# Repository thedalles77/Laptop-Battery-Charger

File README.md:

# Laptop-Battery-Charger
This repository has all the files that I used to repurpose a Dell D630 laptop into a portable Raspberry Pi. 

The Instructable "Battery Powered Raspberry Pi in Repurposed Laptop" is at this url:

https://www.instructables.com/Battery-Powered-Raspberry-Pi-in-Repurposed-Laptop/

The Video "Portable Raspberry Pi Laptop with a Custom Battery Charger" is at this url:

https://vimeo.com/504006511

The Max1873 based battery charge controller board shown below is detailed as a 
Hackster.IO project at this url:

https://www.hackster.io/frank-adams/laptop-battery-charge-controller-e9c3dc

The MP26123 based battery charge controller board shown below is detailed as a 
Hackaday.IO project at this url:

https://hackaday.io/project/177700/details/

A battery fuel gauge using Cairo can be found at this location: 
https://github.com/thedalles77/Raspberry-Pi-easy-drawing

The folders at this repo are organized as follows:

  AT Tiny Supervisor folder contains the AT Tiny 85 code to supervise the charging of a 3 series or 4 series wired battery pack.
  
  Eagle_Board_Files folder contains two folders: One for the Max1873 board and one for the MP26123_4 board. They contain the Eagle layout and schematic, parts list, and test procedure.
  
  Dell_D630_Portable_Pi_KVM folder contains the keyboard matrix and Teensy 3.2 Arduino code for controlling the keyboard, touchpad, and video converter card.
  
  My_Ugly_C_Code folder contains the Pi C code that reads the battery status registers over the SMBus.
  
  USB_SMBUS_CP2112 folder contains the Eagle board files to build a USB to SM Bus bridge for reading the battery status registers. See https://github.com/thedalles77/cp2112_demo for the code to display the battery status registers.
  
  Load_Switch_NCP_45760 folder contains the Eagle board files to build a load switch using the On Semiconductor NCP45760 chip.

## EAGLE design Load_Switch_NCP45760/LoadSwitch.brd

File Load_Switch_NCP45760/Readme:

I had problems getting this NCP45760IMN24RTWG load switch to work but I'll provide the information in case someone else has better luck. 
Let me know if you find a way to make it work.
The Eagle board and schematic files are provided along with pictures.
The 3.3 volt regulator can be an AP7381-33V-A through hole or the AP7381-33Y-13 SMD. The caps are 0805 case size and the resistors are 0603 size.
The loads on the switch were two LM2596 buck regulators that provided 10 volts to the video card and 5 volts to the Pi. 
Each buck regulator had a 100uf cap on its input and a 220uf cap on its output with more caps on the Pi and video card.
The input voltage was 19 Volts DC from a wall supply.
I started with the overcurrent resistor R2 set at 10K and the slew rate capacitor C4 set to 0.01uf but this caused the current protection circuit to trip when first enabled.
Changing the R2 resistor to a short did not change anything but changing the C4 slew rate cap to 1uf allowed the switch to work without tripping the protection circuit.
It ran for 30 minutes and the temperature on the chip and input/output traces stabilized at 52 deg C.
Unfortuantely the load switch would not turn off so I apparently ruined the chip by setting the slew rate to a very slow value.
Even changing the slew rate cap to 0.1uf will still exceed the Energy rating based on the formulas in the data sheet.
This leads me to believe that this chip is not usable for my configuration but it may work fine at lower voltages and/or lower currents.

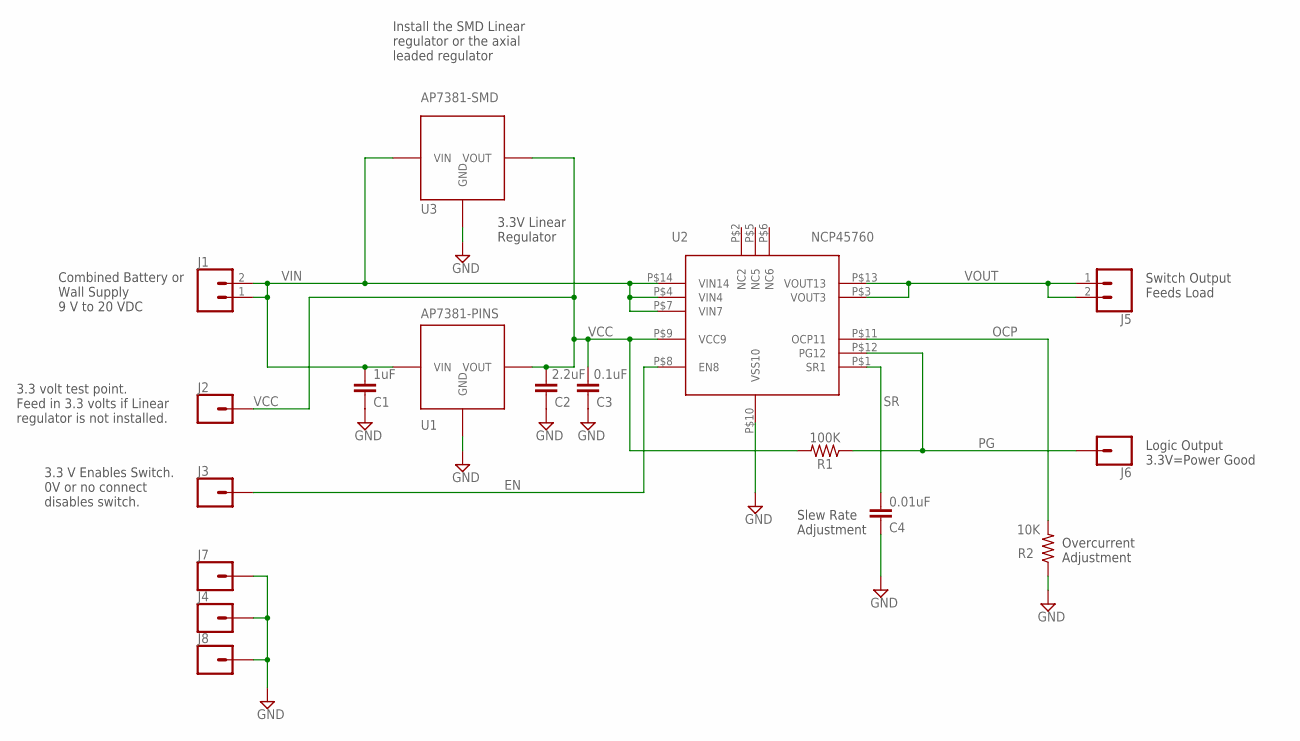
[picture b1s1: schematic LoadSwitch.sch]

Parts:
C1: 1uF; 0805_CAP
C2: 2.2uF; 0805_CAP
C3: 0.1uF; 0805_CAP
C4: 0.01uF; 0805_CAP
J1, J5: CONN_02; 1X02
J2, J3, J4, J6, J7, J8: CONN_01; 1X01
R1: 100K; 0603_RESISTOR
R2: 10K; 0603_RESISTOR
U1: AP7381-PINS; AP7381_PINS
U2: NCP45760
U3: AP7381-SMD; AP7381

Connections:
EN: J3.1, U2.P$8 (EN8)
GND: C1.2, C2.2, C3.2, C4.2, J4.1, J7.1, J8.1, R2.1, U1.P$2 (GND), U2.P$10 (VSS10), U3.P$3 (GND), U3.P$4 (GND)
OCP: R2.2, U2.P$11 (OCP11)
PG: J6.1, R1.1, U2.P$12 (PG12)
SR: C4.1, U2.P$1 (SR1)
VCC: C2.1, C3.1, J2.1, R1.2, U1.P$1 (VOUT), U2.P$9 (VCC9), U3.P$1 (VOUT)
VIN: C1.1, J1.1, J1.2, U1.P$3 (VIN), U2.P$4 (VIN4), U2.P$7 (VIN7), U2.P$14 (VIN14), U3.P$2 (VIN)
VOUT: J5.1, J5.2, U2.P$3 (VOUT3), U2.P$13 (VOUT13)

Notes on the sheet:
3.3V Linear Regulator
Combined Battery or Wall Supply 9 V to 20 VDC
3.3 volt test point. Feed in 3.3 volts if Linear regulator is not installed.
3.3 V Enables Switch. 0V or no connect disables switch.
Slew Rate Adjustment
Overcurrent Adjustment
Switch Output Feeds Load
Logic Output 3.3V=Power Good
Install the SMD Linear regulator or the axial leaded regulator

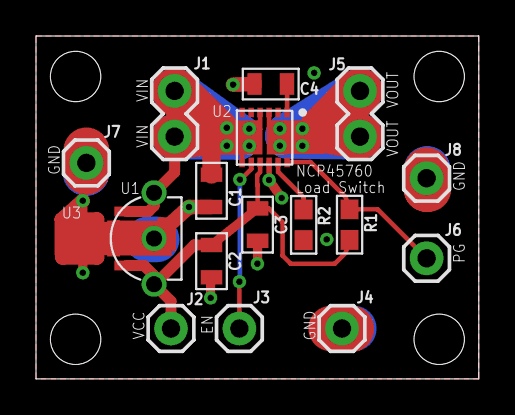
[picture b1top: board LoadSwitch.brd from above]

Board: 2 copper layers, 24.6 x 19.1 mm, 18 parts (1 on the bottom side), 8 nets.

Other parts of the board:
U$1: OSHW_5MM

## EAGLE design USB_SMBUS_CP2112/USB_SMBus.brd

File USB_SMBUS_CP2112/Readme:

See Step 15 of my Instructable for more information regarding the CP2112:
https://www.instructables.com/Battery-Powered-Raspberry-Pi-in-Repurposed-Laptop/
See the forked version of Nick Dademo's repo for the modified code:
https://github.com/thedalles77/cp2112_demo

The Eagle brd file includes the recommended footprint for the slotted holes on the USB connector.
To fabricate this board at OSH Park, upload the zip file which has been run thru a CAM processor to create the proper slotted holes.

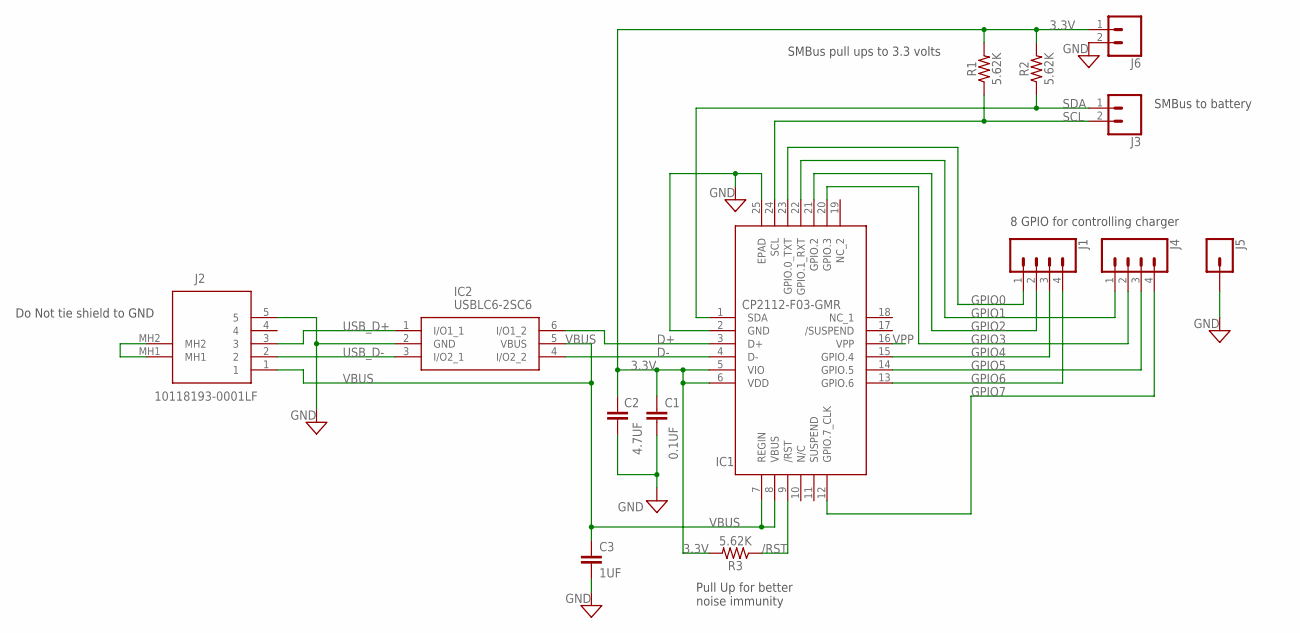
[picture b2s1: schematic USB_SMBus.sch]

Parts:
C1: 0.1UF; 0805_CAP
C2: 4.7UF; 0805_CAP
C3: 1UF; 0805_CAP
IC1: CP2112-F03-GMR; QFN50P400X400X80-25N
IC2: USBLC6-2SC6; SOT95P280X145-6N
J1, J4: CONN_04; 1X04
J2: 10118193-0001LF; 101181930001LF
J3, J6: CONN_02; 1X02
J5: CONN_01; 1X01
R1, R2, R3: 5.62K; 0603_RESISTOR

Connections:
3.3V: C1.1, C2.1, IC1.5 (VIO), IC1.6 (VDD), J6.1, R1.2, R2.2, R3.2
/RST: IC1.9 (/RST), R3.1
D+: IC1.3 (D+), IC2.6 (I/O1_2)
D-: IC1.4 (D-), IC2.4 (I/O2_2)
GND: C1.2, C2.2, C3.2, IC1.2 (GND), IC1.25 (EPAD), IC2.2 (GND), J2.5, J5.1, J6.2
GPIO0: IC1.23 (GPIO.0_TXT), J1.1
GPIO1: IC1.22 (GPIO.1_RXT), J4.1
GPIO2: IC1.21 (GPIO.2), J1.2
GPIO3: IC1.20 (GPIO.3), J4.2
GPIO4: IC1.15 (GPIO.4), J1.3
GPIO5: IC1.14 (GPIO.5), J4.3
GPIO6: IC1.13 (GPIO.6), J1.4
GPIO7: IC1.12 (GPIO.7_CLK), J4.4
unnamed: J2.MH1, J2.MH2
SCL: IC1.24 (SCL), J3.2, R1.1
SDA: IC1.1 (SDA), J3.1, R2.1
USB_D+: IC2.1 (I/O1_1), J2.3
USB_D-: IC2.3 (I/O2_1), J2.2
VBUS: C3.1, IC1.7 (REGIN), IC1.8 (VBUS), IC2.5 (VBUS), J2.1
VPP: IC1.16 (VPP)

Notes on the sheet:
Pull Up for better noise immunity
Do Not tie shield to GND
SMBus to battery
8 GPIO for controlling charger
SMBus pull ups to 3.3 volts

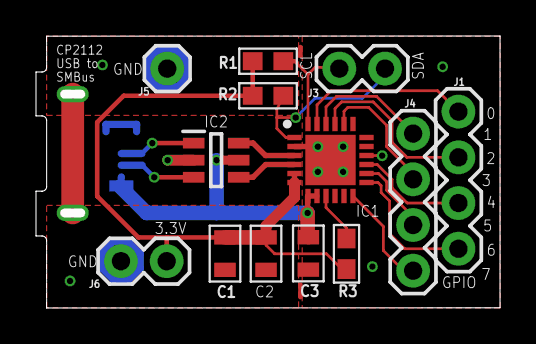
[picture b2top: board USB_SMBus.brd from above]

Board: 2 copper layers, 25.3 x 14.6 mm, 14 parts (1 on the bottom side), 19 nets.

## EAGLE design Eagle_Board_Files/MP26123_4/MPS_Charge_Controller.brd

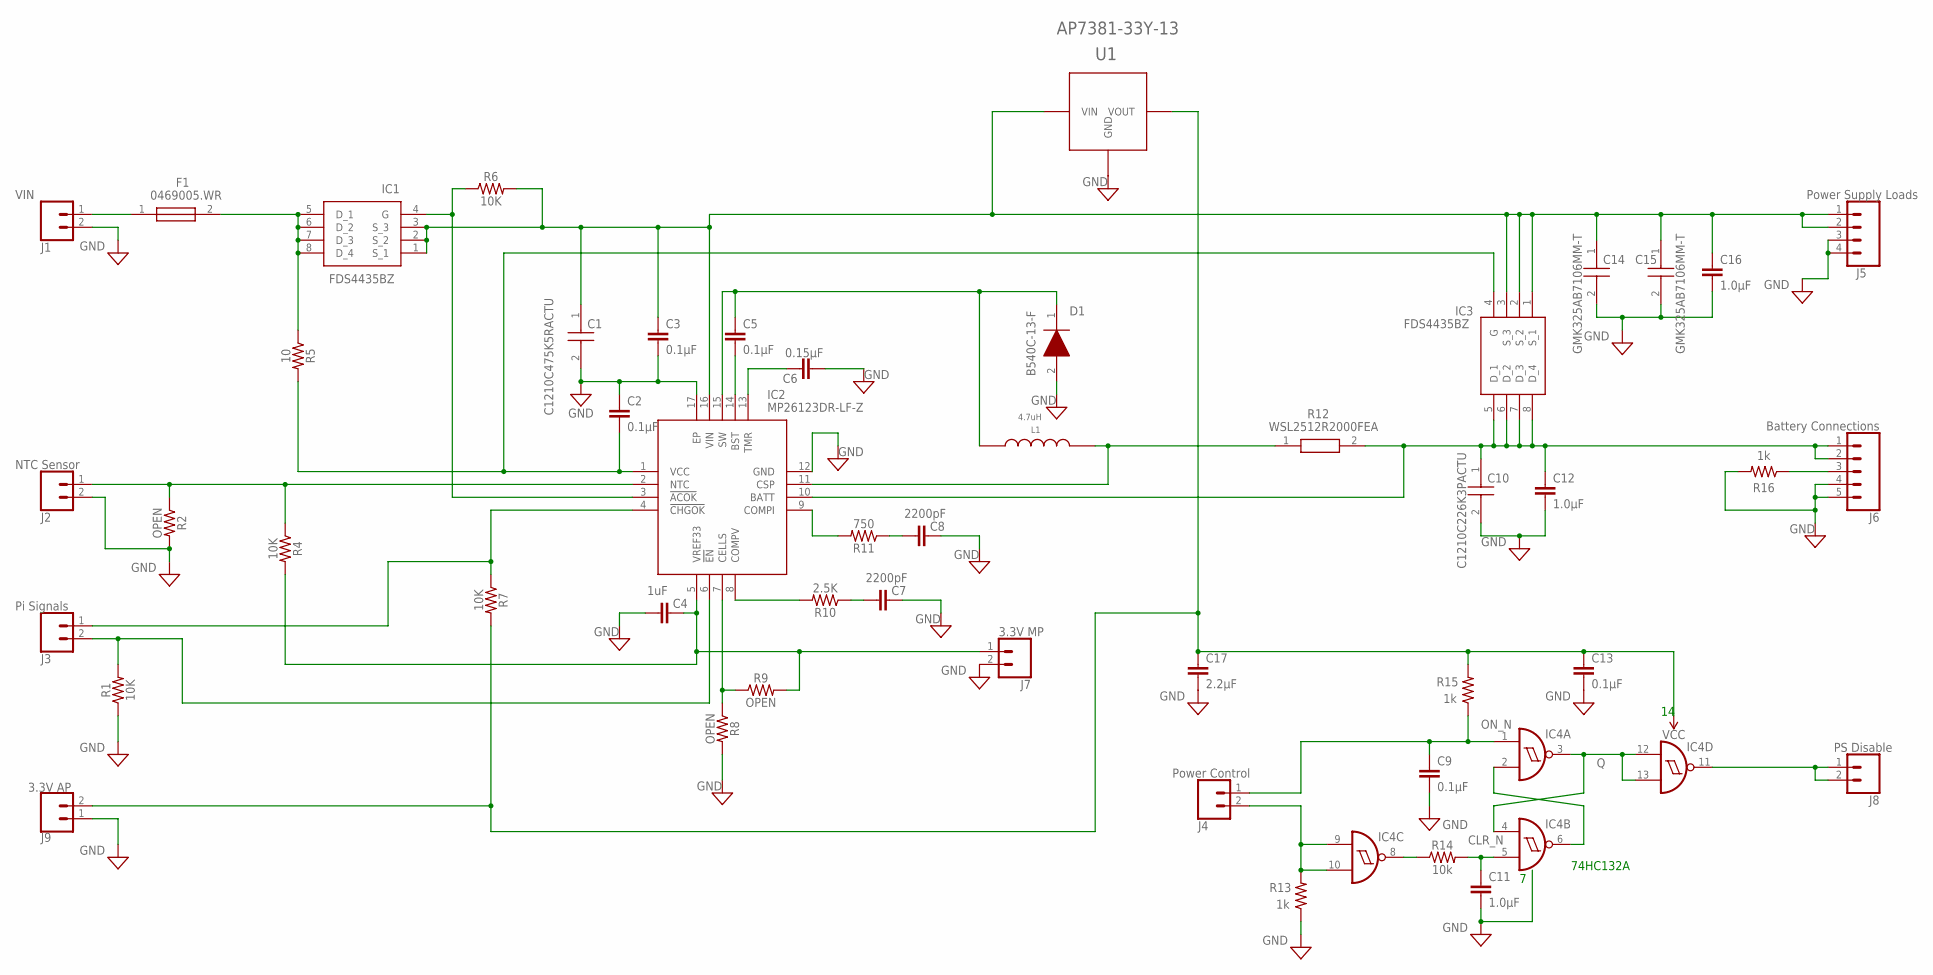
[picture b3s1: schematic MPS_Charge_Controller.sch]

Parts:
C1: C1210C475K5RACTU; CAPC3225X280N
C2, C3, C5, C9, C13: 0.1µF; 0805
C4: 1uF; 0805
C6: 0.15µF; 0805
C7, C8: 2200pF; 0805
C10: C1210C226K3PACTU; CAPC3225X280N
C11, C12, C16: 1.0µF; 0805
C14, C15: GMK325AB7106MM-T; CAPC3225X270N
C17: 2.2µF; 0805
D1: B540C-13-F; DIOM7959X250N
F1: 0469005.WR; FUSC3216X105N
IC1, IC3: FDS4435BZ; SOIC127P600X175-8N
IC2: MP26123DR-LF-Z; QFN65P400X400X100-17N
IC4: 74132D; SO14
J1: VIN; 1X02
J2: NTC Sensor; 1X02
J3: Pi Signals; 1X02
J4: Power Control; 1X02
J5: Power Supply Loads; 1X04
J6: Battery Connections; 1X05
J7: 3.3V MP; 1X02
J8: PS Disable; 1X02
J9: 3.3V AP; 1X02
L1: 4.7uH; NRS8030
R1, R4, R6, R7: 10K; 0603_RESISTOR
R2, R8, R9: OPEN; 0603_RESISTOR
R5: 10; 0603_RESISTOR
R10: 2.5K; 0603_RESISTOR
R11: 750; 0603_RESISTOR
R12: WSL2512R2000FEA; RESC6332X71N
R13, R15, R16: 1k; 0603
R14: 10k; 0603
U1: AP7381-33Y-13; AP7381

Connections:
BATTERY: C10.1, C12.1, IC2.10 (BATT), IC3.5 (D_1), IC3.6 (D_2), IC3.7 (D_3), IC3.8 (D_4), J6.1, J6.2, R12.2
BST: C5.2, IC2.14 (BST)
CELLS: IC2.7 (CELLS), R8.1, R9.1
CHGOK: IC2.4 (!CHGOK), J3.1, R7.1
CLR_N: C11.1, IC4.5 (I1), R14.2
COMPI: IC2.9 (COMPI), R11.2
COMPV: IC2.8 (COMPV), R10.2
CURRENT_SENSE_P: IC2.11 (CSP), L1.P$2, R12.1
DISABLE: IC2.6 (!EN), J3.2, R1.2
FUSE_OUT: F1.2, IC1.5 (D_1), IC1.6 (D_2), IC1.7 (D_3), IC1.8 (D_4), R5.1
GND: C1.2, C2.1, C3.2, C4.2, C6.2, C7.1, C8.1, C9.2, C10.2, C11.2, C12.2, C13.2, C14.2, C15.2, C16.2, C17.2, D1.2 (A), IC2.12 (GND), IC2.17 (EP), IC4.7 (GND), J1.2, J2.2, J5.3, J5.4, J6.4, J6.5, J7.2, J9.1, R1.1, R2.2, R8.2, R13.1, R16.2, U1.P$3 (GND), U1.P$4 (GND)
INPUT_GATE: IC1.4 (G), IC2.3 (!ACOK), R6.1
INTERNAL_SW: C5.1, D1.1 (K), IC2.15 (SW), L1.P$1
MP3V3: C4.1, IC2.5 (VREF33), J7.1, R4.2, R9.2
unnamed: C8.2, R11.1
unnamed: C7.2, R10.1
unnamed: F1.1, J1.1
NTC: IC2.2 (NTC), J2.1, R2.1, R4.1
ON_N: C9.1, IC4.1 (I0), J4.1, R15.1
PS_DISABLE: IC4.11 (O), J8.1, J8.2
Q: IC4.3 (O), IC4.4 (I0), IC4.12 (I0), IC4.13 (I1)
QBAR: IC4.2 (I1), IC4.6 (O)
SYSTEM_PRESENT: J6.3, R16.1
TMR: C6.1, IC2.13 (TMR)
TURN_OFF: IC4.9 (I0), IC4.10 (I1), J4.2, R13.2
TURN_OFF_N: IC4.8 (O), R14.1
V3P3: C13.1, C17.1, IC4.14 (VCC), J9.2, R7.2, R15.2, U1.P$1 (VOUT)
VCC: C2.2, IC2.1 (VCC), IC3.4 (G), R5.2
VLOAD: C1.1, C3.1, C14.1, C15.1, C16.1, IC1.1 (S_1), IC1.2 (S_2), IC1.3 (S_3), IC2.16 (VIN), IC3.1 (S_1), IC3.2 (S_2), IC3.3 (S_3), J5.1, J5.2, R6.2, U1.P$2 (VIN)

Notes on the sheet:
74HC132A

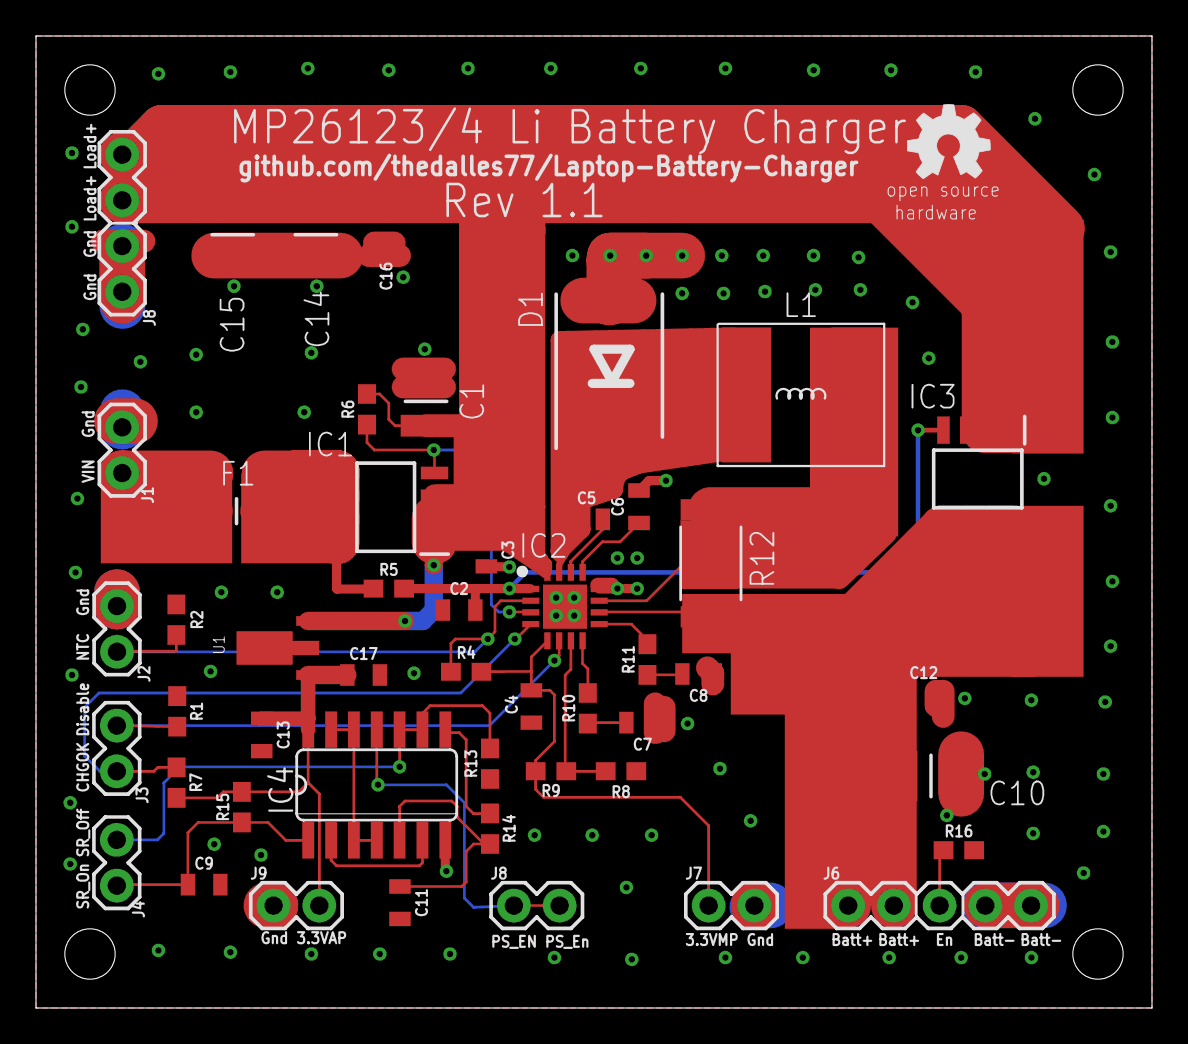
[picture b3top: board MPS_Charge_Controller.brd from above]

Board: 2 copper layers, 62.0 x 54.0 mm, 50 parts (0 on the bottom side), 29 nets.

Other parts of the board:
U$1: OSHW_5MM

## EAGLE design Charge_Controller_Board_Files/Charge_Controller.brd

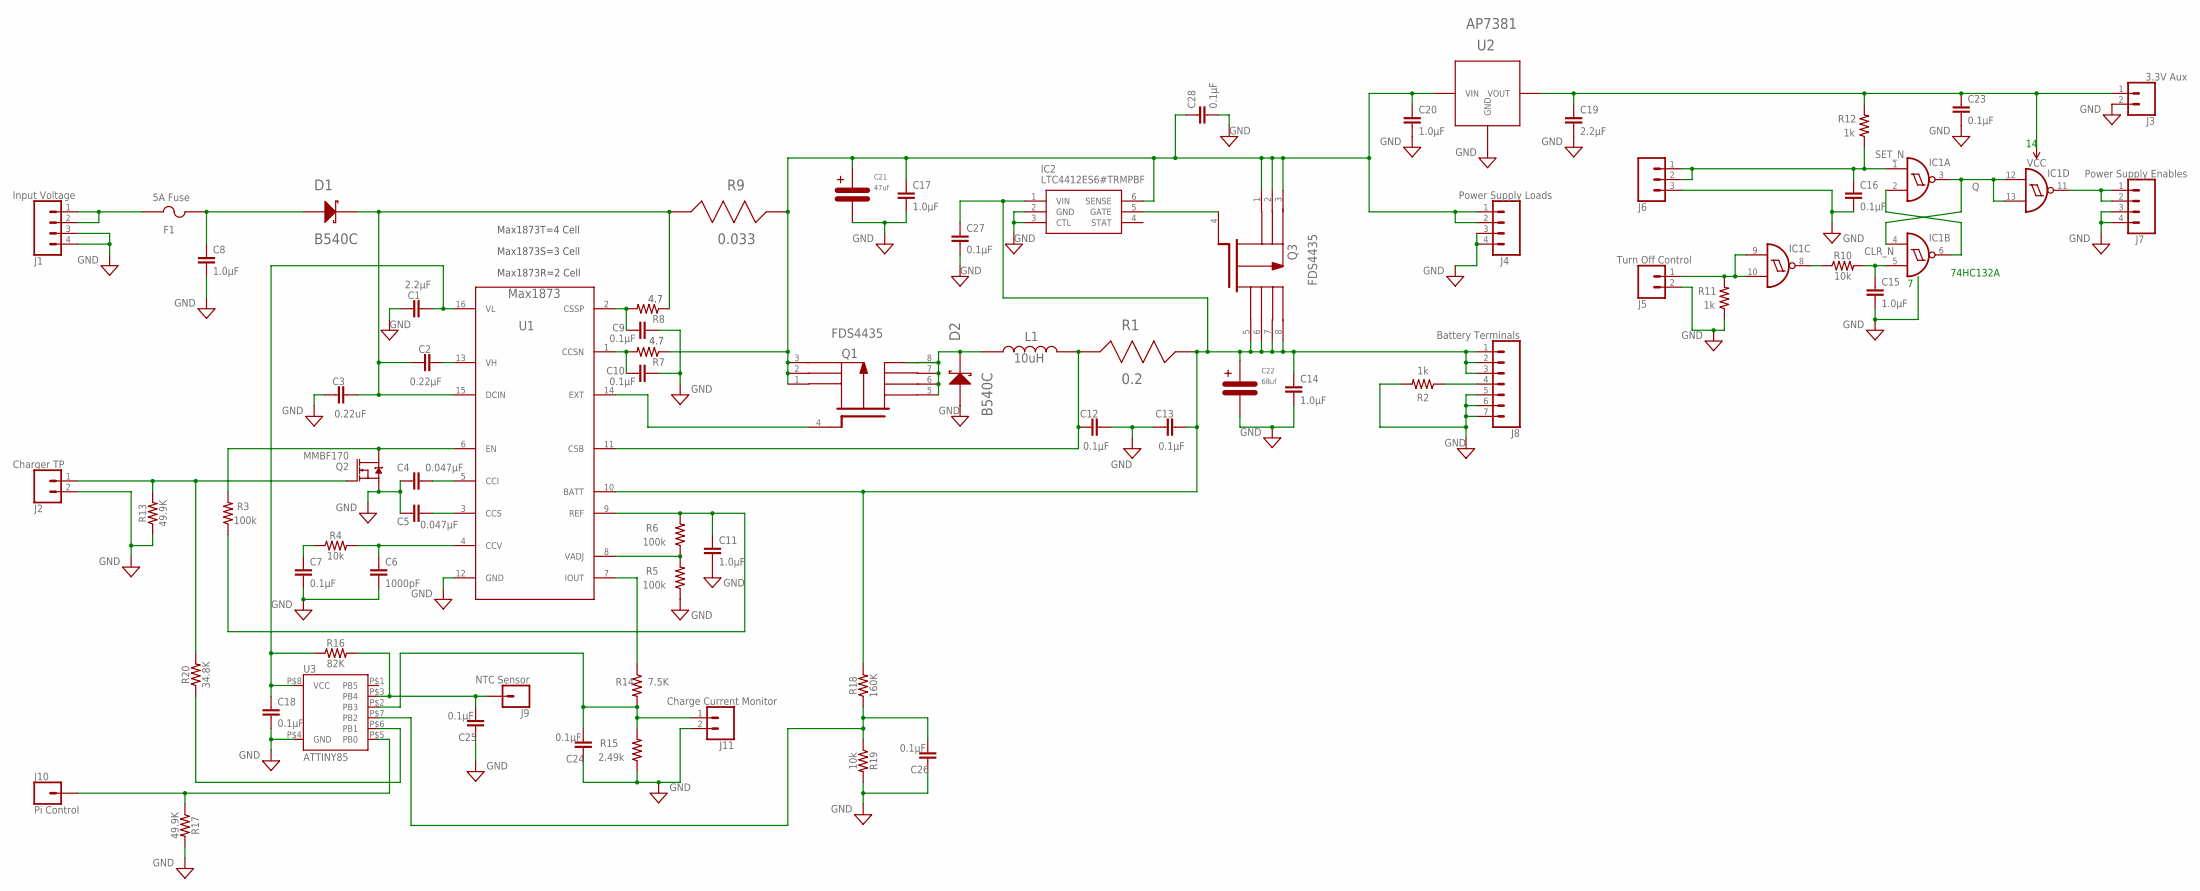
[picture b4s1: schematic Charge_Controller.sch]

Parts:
C1, C19: 2.2µF; 0805
C2: 0.22µF; 0805
C3: 0.22uF; 0805
C4, C5: 0.047µF; 0805
C6: 1000pF; 0805
C7, C9, C10, C12, C13, C16, C18, C23, C24, C25, C26, C27, C28: 0.1µF; 0805
C8, C11, C14, C15, C17, C20: 1.0µF; 0805
C21: 47uf; 2917
C22: 68uf; 2917
D1, D2: B540C
F1: 5A Fuse; FUSE1206
IC1: 74132D; SO14
IC2: LTC4412ES6#TRMPBF; SOT95P280X100-6N
J1: Input Voltage; 1X04
J2: Charger TP; 1X02
J3: 3.3V Aux; 1X02
J4: Power Supply Loads; 1X04
J5: Turn Off Control; 1X02
J6: Turn On; 1X03
J7: Power Supply Enables; 1X04
J8: Battery Terminals; 1X07
J9: NTC Sensor; 1X01
J10: Pi Control; 1X01
J11: Charge Current Monitor; 1X02
L1: 10uH; NRS8030
Q1, Q3: FDS4435
Q2: MMBF170
R1: 0.2; 2512
R2, R11, R12: 1k; 0603
R3, R5, R6: 100k; 0603
R4, R10, R19: 10k; 0603
R7, R8: 4.7; 0603_4P7
R9: 0.033; 2512
R13: 49.9K; 0603_RESISTOR
R14: 7.5K; 0603_RESISTOR
R15: 2.49k; 0603
R16: 82K; 0603_RESISTOR
R17: 49.9K; 0603
R18: 160K; 0603_RESISTOR
R20: 34.8K; 0603_RESISTOR
U1: Max1873; MAX1873
U2: AP7381
U3: ATTINY85

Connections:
BATT: C13.2, C14.1, C22.POS, C27.1, IC2.1 (VIN), J8.1, J8.2, J8.3, Q3.5 (D5), Q3.6 (D6), Q3.7 (D7), Q3.8 (D8), R1.P$2, R18.2, U1.10 (BATT)
BATT_ENABLE: J8.4, R2.1
BATT_ISENSE: C12.1, L1.P$2, R1.P$1, U1.11 (CSB)
CCI: C4.2, U1.5 (CCI)
CCS: C5.2, U1.3 (CCS)
CCSN: C10.1, R7.2, U1.1 (CCSN)
CCV: C6.1, R4.2, U1.4 (CCV)
CCV_MID: C7.1, R4.1
CHARGE_DISABLE: R20.1, U3.P$6 (PB1)
CHARGE_MONITOR: C24.2, J11.1, R14.2, R15.2, U3.P$2 (PB3)
CLR_N: C15.1, IC1.5 (I1), R10.2
CSSP: C9.1, R8.2, U1.2 (CSSP)
DIODE_GATE: IC2.5 (GATE), Q3.4 (G4)
DISABLE_GATE: J2.1, Q2.1 (G), R13.2, R20.2
EN: Q2.3 (D), R3.2, U1.6 (EN)
FET_D: D2.P$2, L1.P$1, Q1.5 (D5), Q1.6 (D6), Q1.7 (D7), Q1.8 (D8)
FET_G: Q1.4 (G4), U1.14 (EXT)
GND: C1.1, C3.1, C4.1, C5.1, C6.2, C7.2, C8.2, C9.2, C10.2, C11.2, C12.2, C13.1, C14.2, C15.2, C16.2, C17.2, C18.2, C19.2, C20.2, C21.NEG, C22.NEG, C23.2, C24.1, C25.1, C26.1, C27.2, C28.2, D2.P$1, IC1.7 (GND), IC2.2 (GND), IC2.3 (CTL), J1.3, J1.4, J2.2, J3.2, J4.3, J4.4, J5.2, J6.3, J7.3, J7.4, J8.5, J8.6, J8.7, J11.2, Q2.2 (S), R2.2, R5.1, R11.1, R13.1, R15.1, R17.2, R19.2, U1.12 (GND), U2.P$3 (GND), U2.P$4 (GND), U3.P$4 (GND)
INPUT_V: F1.P$1, J1.1, J1.2
unnamed: R14.1, U1.7 (IOUT)
NTC: C25.2, J9.1, R16.2, U3.P$3 (PB4)
PI_CONTROL: J10.1, R17.1, U3.P$5 (PB0)
PS_EN: IC1.11 (O), J7.1, J7.2
Q: IC1.3 (O), IC1.4 (I0), IC1.12 (I0), IC1.13 (I1)
QBAR: IC1.2 (I1), IC1.6 (O)
REF: C11.1, R3.1, R6.2, U1.9 (REF)
SET_N: C16.1, IC1.1 (I0), J6.1, J6.2, R12.1
TURN_OFF: IC1.9 (I0), IC1.10 (I1), J5.1, R11.2
TURN_OFF_N: IC1.8 (O), R10.1
VADJ: R5.2, R6.1, U1.8 (VADJ)
VBAT_DIV: C26.2, R18.1, R19.1, U3.P$7 (PB2)
VCC: C19.1, C23.1, IC1.14 (VCC), J3.1, R12.2, U2.P$1 (VOUT)
VH: C2.2, U1.13 (VH)
VIN_DIODE: C2.1, C3.2, D1.P$2, R8.1, R9.P$2, U1.15 (DCIN)
VIN_FUSE: C8.1, D1.P$1, F1.P$2
VL: C1.2, C18.1, R16.1, U1.16 (VL), U3.P$8 (VCC)
VLOAD: C17.1, C20.1, C21.POS, C28.1, IC2.6 (SENSE), J4.1, J4.2, Q1.1 (S1), Q1.2 (S2), Q1.3 (S3), Q3.1 (S1), Q3.2 (S2), Q3.3 (S3), R7.1, R9.P$1, U2.P$2 (VIN)

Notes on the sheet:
74HC132A
4.7
Max1873T=4 Cell
Max1873S=3 Cell
Max1873R=2 Cell

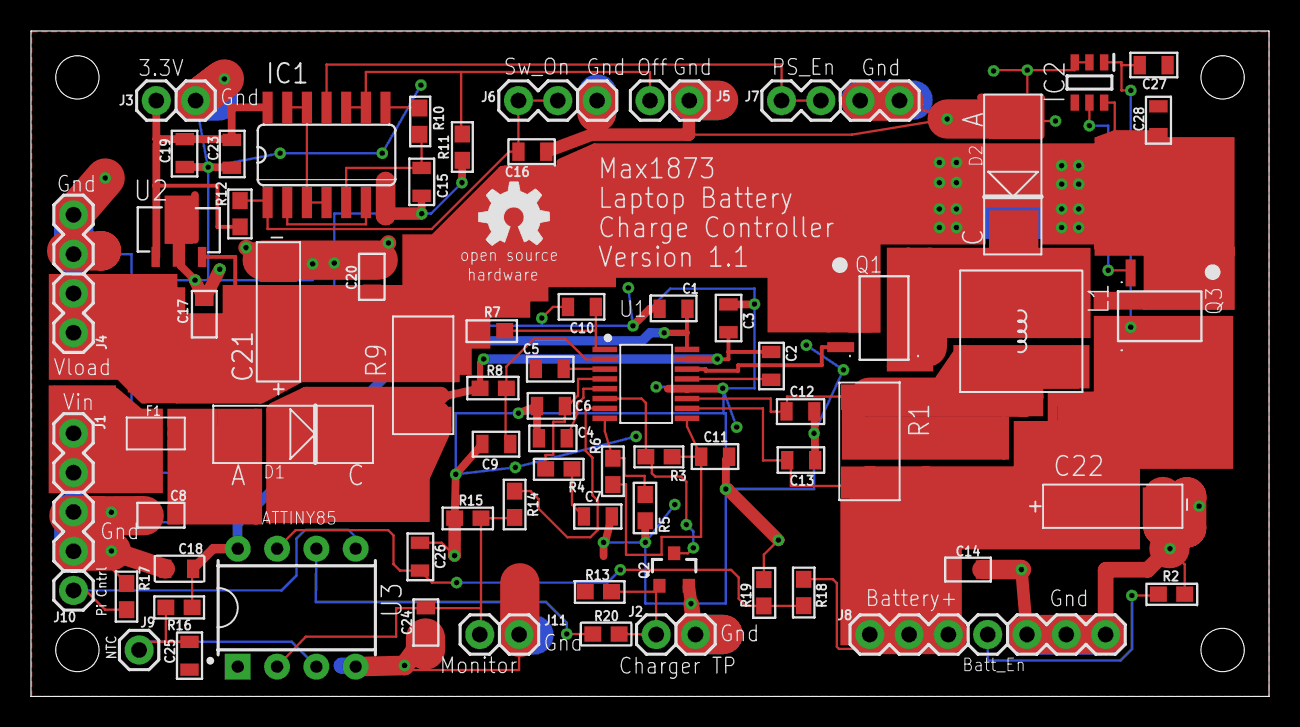
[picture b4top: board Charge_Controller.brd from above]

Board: 2 copper layers, 80.0 x 43.0 mm, 72 parts (0 on the bottom side), 37 nets.

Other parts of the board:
U$1: OSHW_5MM

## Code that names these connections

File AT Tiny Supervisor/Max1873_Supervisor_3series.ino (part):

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   See the License for the specific language governing permissions and
   limitations under the License.
*/
// This ATTiny85 program controls the enable pin on the Max1873 so it will safely charge the Li+ laptop battery in a 3 series pack.
// Assumptions: 
//    a. Maximum battery charge current is set at 1 amp.
//    b. Battery Pack has 3 series cells, each cell fully charged at 4.2 volts, giving a pack voltage of 12.6 volts.
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// July 1, 2020  Original Release

// ATTiny Logic Pins
#define pi_turnoff 0 // Pin 5 PB0 is an input. 1=turnoff. PCB has external pull down resistor
#define max_en 1 // Pin 6 PB1 drives BS170 NFET that turns Max1873 on and off. 0=On, 1=Off
// ATTiny Analog Pins
#define Vbat A1 // Pin 7 ADC1 receives divided down battery pack voltage
#define bat_temp A2 // Pin 3 ADC2 receives divided down battery temperature voltage
#define iout A3 // Pin 2 ADC3 receives divided down Max1873 Iout voltage
// Battery charging values
#define precharge 492 // this is a battery voltage of 9 volts. Pulse charge until voltage is above this level.
#define trickle 233 // Trickle charge trip level that turns off the charger. 233=250ma charge current
#define no_charge 11 // Near zero "no-charge" level equates to 12ma
#define temp_limit 150 // 150 is roughly a 10 degree temperature increase
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void setup()
{
  analogReference(INTERNAL1V1); // use the 1.1 volt reference in the ATTiny for the ADC  
  pinMode(Vbat, INPUT); // divided down battery voltage is input to the ADC on this pin
  pinMode(bat_temp, INPUT); // voltage divider with NTC thermister is input to the ADC on this pin
  pinMode(iout, INPUT); // divided down voltage from the Max1873 Iout signal is input to the ADC on this pin
  pinMode(pi_turnoff, INPUT); // Pi drives this logic input to 3.3V to turn off the Max1873. Pull down resistor on PCB
  pinMode(max_en, OUTPUT); // charge control output signal drives gate of BS170 NFET. NFET turned on will disable Max1873
  digitalWrite(max_en, HIGH); // keep charger off initially
  delay(2000); // wait to let the battery temperature and voltage stabilize
// Save initial battery temperature
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
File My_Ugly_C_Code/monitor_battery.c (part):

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*/
// The program will monitor battery state of charge every 30 seconds and 
// issue a sudo shutdown -h now command if the battery is nearly empty.
// At 15% SoC, the blue LED turns on constantly to indicate a low battery warning. 
// At 10% SoC, the LCD blinks off and on every 30 seconds to get the users attention. 
// At 8% SoC, a safe shutdown is executed.
// 
// This program reads the laptop battery status registers over a bit-
// bang SMBus created with two of the Pi's GPIO pins and wiringPi. 
// SMBus Data and clock are pulled to 3.3 volts with resistors on the Pi.
// Data is wired from Pi GPIO 2 to Dell D630 battery pin 4.
// Clock is wired from Pi GPIO 3 to Dell D630 battery pin 3.
//
// Revision History - The previous version of this code was for a
// Pi-Teensy laptop made from a Sony Vaio. It is documented at
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#include <wiringPi.h>

// Pin number declarations
#define clock 3 // SMBus clock on Pin 5, GPIO3
#define data 2 // SMBus data on Pin 3, GPIO2
#define lcd_pwr 4 // Toggle LCD power on/off Pin 7, GPIO 4 (active low)
#define led_cntrl 17 // Blue LED Control Pin 11, GPIO 17 (active high)
#define charge_dis 19 // Disable Max1873 battery charger Pin 35,GPIO 19 (active high)
#define lcd_status 22 // Pin 15, GPIO 22 Shows if LCD is on (3.3 V) or off (0 v)

// time constants
#define quarter 10 // quarter period time in usec

// Global variables
_Bool error = 0; // set to 1 when battery gives a NACK

// Functions
void go_z(int pin) // float the pin and let pullup or battery set level
{
	pinMode(pin, INPUT); // set pin as input to tri-state the driver
}
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	go_z(clock); // clock high
	// read data to see if battery sends a low (acknowledge transfer)
	if (read_pin(data)) {  // is the data bit high?
	  error = 1; // battery did not acknowledge the transfer
	}
	delayMicroseconds(quarter * 2);
	go_0(clock); // clock low
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		go_z(lcd_pwr); // release power signal so pull up brings it high
	}
	int soc; // variable to store the state of charge
	int old_soc = 50; // soc from last time battery was checked (start at mid scale)
	unsigned short bat_stat; // variable to store the battery status
	_Bool bad_bat_stat = 0; // 
	char over_temp_count = 0; // count consecutive overtemp loops 
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
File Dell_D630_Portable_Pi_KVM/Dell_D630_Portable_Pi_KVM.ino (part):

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#define VIDEO_MENU 15 // Video converter card - Menu signal on pad K4 
#define VIDEO_RIGHT 32 // Video converter card - Right signal on pad K1
//
#define TURN_OFF 13 // Teensy drives this output high to disable power supplies
#define PI_CONTROL 29 // Pi drives this logic signal low when it wants to shut down
//
const byte rows_max = 18; // sets the number of rows in the matrix
const byte cols_max = 8; // sets the number of columns in the matrix
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
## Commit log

2021-10-15 Update LICENSE
    Added Solderpad hardware license 2.1

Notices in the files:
AT Tiny Supervisor/Max1873_Supervisor_3series.ino:
Copyright 2021 Frank Adams
Licensed under the Apache License, Version 2.0 (the "License");
Dell_D630_Portable_Pi_KVM/Dell_D630_Portable_Pi_KVM.ino:
Copyright 2019 Frank Adams
My_Ugly_C_Code/monitor_battery.c:
Copyright 2020 Frank Adams
parts and their libraries:
SparkFun-Capacitors: Licensing: Creative Commons ShareAlike 4.0 International - https://creativecommons.org/licenses/by-sa/4.0
